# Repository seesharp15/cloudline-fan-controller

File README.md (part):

# Cloudline AI-CLS6 fan controller

A stand-alone speed controller for the **AC Infinity Cloudline AI-CLS6**
(Cloudline S6) EC inline fan. It uses an **Arduino Nano** and an **AITRIP
1.3″ OLED module with a built-in EC11 rotary encoder**, plugs into the fan's
4-pin Molex control lead in place of the stock controller, and runs entirely
from the fan's own 10 V supply.

| Fan off | Fan running (calibrated) |
|---|---|
|  |  |

## What it does

- **Turn the knob** to set the speed from 0 to 100 %: 1 % per click, or 5 %
  per click when you spin it quickly.
- **Press the knob** to switch the fan on or off.
- **The fan is always off at power-up.** A resistor guarantees this in
  hardware before the Arduino even starts, and the firmware starts OFF.
- **The speed setting is kept while the controller has power.** Off and on
  again returns to the same speed. After a power cut it starts OFF at 50 %.
  Nothing is stored permanently.
- **The display shows:**
  - ON/OFF status in the title bar, which turns solid while the fan is on;
  - **SET**: the speed you asked for, as a bar and a percentage;
  - **ACT**: the measured speed from the fan's tachometer, as a bar and a
    percentage of the fan's calibrated top speed;
  - the measured **RPM**.
- **Power:** taken from the fan's +10 V through a resettable fuse,
  reverse-polarity diode, surge clamp and filtering. The controller draws
  about 35–60 mA.
- **Safety nets:** a watchdog stops the fan and restarts the controller if
  the program ever hangs; a "NO TACH / STALLED" warning appears if the fan is
  told to run but no speed pulses arrive.

> ⚠️ **Read before you build.** AC Infinity does not publish the electrical
> details of the control port. The pin functions and signal levels in this
> project come from other builders' reports, and **whether the 4-pin port
> carries a tachometer signal at all is unconfirmed**. The
> [pre-connection verification](#pre-connection-verification) below takes
> about 20 minutes with a multimeter and tells you whether your fan matches.
> Without a tach signal everything works except the ACT bar and RPM.
> [VERIFICATION.md](VERIFICATION.md) lists exactly what has and has not been
> verified.

## Contents

1. [Documents in this repository](#documents-in-this-repository)
2. [Bill of materials](#bill-of-materials)
3. [Tools](#tools)
4. [Software setup](#software-setup)
5. [Pre-connection verification](#pre-connection-verification)
6. [Step-by-step build](#step-by-step-build) (steps 1–6, then
   [7. first power-up](#step-7-first-power-up-on-the-fan-supply) and
   [8. enclosure](#step-8-fit-it-in-the-enclosure))
8. [Normal operation](#normal-operation)
9. [Troubleshooting](#troubleshooting)
10. [Development and tests](#development-and-tests)
11. [Sources](#sources)

---

## Documents in this repository

| Document | Contents |
|---|---|
| [PINOUT.md](PINOUT.md) | Every pin of every part, power rails, point-to-point wiring list |
| [hardware/schematic.svg](hardware/schematic.svg) ([PNG](hardware/schematic.png)) | Full schematic, every part labelled with reference and value |
| [hardware/wiring.svg](hardware/wiring.svg) ([PNG](hardware/wiring.png)) | Physical wiring view with suggested wire colours, for people who don't read schematics |
| [hardware/bom.csv](hardware/bom.csv) | Parts list with part numbers and prices |
| [hardware/pcb/](hardware/pcb/README.md) | **Single-sided PCB** (1 copper layer) as an alternative to perfboard: KiCad project, Gerbers + drill ready to order, assembly drawing, ordering options |
| [hardware/pcb/fusion/](hardware/pcb/fusion/README.md) | **Milling the PCB in Fusion 360** on a Stepcraft M.1000: STEP + DXF (isolation paths, drill layers), Fusion tool library, CAM setup for UCCNC |
| [hardware/pcb/eagle/](hardware/pcb/eagle/README.md) | **Editable design for Fusion Electronics**: schematic + board in EAGLE format |
| [FAQ.md](FAQ.md) | The questions builders ask: USB + fan power, PWM frequency, other fans, warranty, other boards… |
| [BENCH_TEST.md](BENCH_TEST.md) | Manual test of every requirement, first with a dummy load, then with the fan |
| [VERIFICATION.md](VERIFICATION.md) | Requirements traceability, electrical calculations, pin cross-check, what is verified versus assumed, known limitations, review findings |
| [CHANGELOG.md](CHANGELOG.md) | Changes |
| [firmware/](firmware/) | Arduino sketch. Every setting is in [`config.h`](firmware/cloudline_controller/config.h) |
| [test/](test/) | Host unit tests and simulations ([how to run](test/README.md)) |
| [sim/](sim/) | Wokwi simulator files ([what can and cannot be simulated](sim/README.md)) |

---

## Bill of materials

Prices are approximate (USD, 2026) for single quantities. The full list with
manufacturer part numbers is in [hardware/bom.csv](hardware/bom.csv). Any
part with the same value and rating works; the part numbers are examples.

| Ref | Qty | Part | Value / rating | Example part number | ≈ Cost |
|---|---|---|---|---|---|
| U1 | 1 | Arduino Nano | ATmega328P, 5 V, 16 MHz (CH340 clone is fine) | Arduino A000005, or ELEGOO Nano V3.0 | $8 (clone) |
| U3 | 1 | 1.3″ OLED + EC11 module | SH1106, 128×64, I²C 0x3C, 3.3 V | AITRIP 1.3″ OLED with EC11 (Amazon ASIN B0F87DZ51P) | $10 |
| U2 | 1 | 3.3 V LDO regulator | 250 mA, V<sub>in</sub> ≤ 6 V, TO-92 | Microchip MCP1700-3302E/TO | $0.45 |
| Q1 | 1 | N-channel MOSFET | 60 V, 200 mA, logic-level, TO-92 | onsemi 2N7000TA | $0.30 |
| D1 | 1 | Schottky diode | 1 A, 20 V | 1N5817 | $0.20 |
| D2 | 1 | TVS diode, unidirectional | V<sub>RWM</sub> 11.1 V, 600 W | Littelfuse P6KE13A (P6KE15A if your fan measures > 10.8 V) | $0.45 |
| D3, D4 | 2 | Small Schottky diode | 30 V, 200 mA | BAT85 | $0.30 |
| F1 | 1 | Resettable PTC fuse | 0.2 A hold, 0.4 A trip | Bourns MF-R020 | $0.35 |
| U4 | 1 | I²C level shifter module (BSS138) | 5 V ↔ 3.3 V, bidirectional, 2 channels used | SparkFun BOB-12009 | $4 |
| C1 | 1 | Electrolytic capacitor | 220 µF, 25 V | Panasonic EEU-FR1E221 | $0.40 |
| C2 | 1 | Ceramic capacitor | 100 nF, 50 V, 5 mm lead pitch | TDK FG28X7R1H104KNT06 | $0.25 |
| C3, C4 | 2 | Ceramic capacitor | 1 µF, 25 V, 5 mm lead pitch | TDK FG28X7R1E105KRT06 | $0.60 |
| C5 | 1 | Ceramic capacitor | 10 nF, 50 V, 5 mm lead pitch | TDK FG28X7R1H103KNT06 | $0.25 |
| R1, R2 | 2 | Resistor ¼ W 5 % | 2.2 kΩ | Yageo CFR-25JB-52-2K2 | $0.20 |
| R3 | 1 | Resistor ¼ W 5 % | 220 Ω | Yageo CFR-25JB-52-220R | $0.10 |
| R4, R6 | 2 | Resistor ¼ W 5 % | 10 kΩ | Yageo CFR-25JB-52-10K | $0.20 |
| R5 | (1) | Resistor ¼ W 5 %, **only if check M3 says so** | 4.7 kΩ | Yageo CFR-25JB-52-4K7 | $0.10 |
| R7 | 1 | Resistor ¼ W 5 % | 1 kΩ | Yageo CFR-25JB-52-1K0 | $0.10 |
| J1 | 1 | 4-pin PC "Molex" extension cable | male-to-female, 18–20 AWG | StarTech.com LP4POWEXT12 | $4 |
| — | 1 | Perfboard | 5 × 7 cm, 2.54 mm pitch | any | $1 |
| — | 2 | Female header strip (Nano socket) | 1 × 15, 2.54 mm | Sullins PPTC151LFBN-RC | $2 |
| — | 10 | Female-female jumper wires | 20 cm Dupont, for the OLED module | any | $3 |
| — | — | Hook-up wire | 22 AWG stranded (power), 24–26 AWG stranded (signals), several colours | any silicone wire kit | $8 |
| — | — | Heat-shrink tubing | 2–6 mm assortment, 2:1 | any | $6 |
| — | 1 | Enclosure | ABS box, **inside** at least 75 × 60 × 35 mm (perfboard) or 115 × 90 × 35 mm (PCB, so its corners clear the box's screw posts) | a Hammond 1591-series size chosen from its drawing, or 3D-printed | $8 |
| — | 1 | Cable gland | PG7 | any | $0.50 |
| — | 4 | Nylon standoffs and screws | M2.5 or M3 | any | $1 |
| | | | | **Total** | **≈ $60** |

## Tools

| Tool | Notes |
|---|---|
| Temperature-controlled soldering iron | 330–360 °C, small chisel tip |
| Solder | 0.6–0.8 mm rosin-core |
| **Digital multimeter** | Must measure DC volts, resistance, continuity and **diode test**. A frequency (Hz) range is useful for the tach check but not essential. |
| Wire strippers, flush cutters, tweezers | |
| Heat gun or lighter | For heat-shrink |
| **USB cable for the Nano** | Usually **Mini-USB** (some clones use Micro-USB or USB-C). It must be a **data** cable, not charge-only. |
| Computer | Windows, macOS or Linux, with Arduino IDE 2.x |
| 9 V battery with snap lead (or a 9–10 V bench supply with current limit) | For testing the power section before anything touches the fan. Optional but recommended. |
| 220 Ω 1 W resistor, 4.7 kΩ and 10 kΩ ¼ W resistors, 100 Ω ¼ W resistor | For the pre-connection checks (spares from the parts list work) |
| Small drill / step bit, file | For the enclosure window and knob hole |

---

## Software setup

1. **Install the Arduino IDE 2.x** from <https://www.arduino.cc/en/software>
   (2.3.x or newer).
2. **Board support.** Open *Tools → Board → Boards Manager*, search for
   **Arduino AVR Boards**, and install version **1.8.6**. (It is usually
   already installed; just check the version.)
3. **Library.** Open *Tools → Manage Libraries*, search for **U8g2** (by
   oliver), choose version **2.35.30** in the version drop-down, and click
   *Install*. No other library is needed. The pinned versions are listed in
   [firmware/libraries.txt](firmware/libraries.txt).
4. **Open the sketch.** *File → Open* →
   `firmware/cloudline_controller/cloudline_controller.ino`. Five tabs open:
   `cloudline_controller.ino`, `app.cpp`, `config.h`, `display_ui.h`,
   `fan_logic.h`. The folder must stay named `cloudline_controller`.
5. **Select the board.** *Tools → Board → Arduino AVR Boards → Arduino
   Nano*.
6. **USB driver (clone Nanos).** Most clones use a **CH340** USB chip. Plug
   the Nano in and look at *Tools → Port*:
   - A new port appears (`COM3`… on Windows, `/dev/cu.usbserial-…` or
     `/dev/cu.wchusbserial…` on macOS, `/dev/ttyUSB0` on Linux): fine, select it.
   - No new port: install the CH340 driver (**CH341SER**) from the chip maker,
     WCH: <https://www.wch-ic.com/downloads/CH341SER_EXE.html> (Windows) or
     <https://www.wch-ic.com/downloads/CH341SER_MAC_ZIP.html> (macOS), then
     replug. Linux needs no driver. If still nothing, try another USB cable:
     many are charge-only.
7. **Processor setting.** *Tools → Processor* has two choices:
   - **"ATmega328P"**: genuine Nanos and newer clones (Optiboot bootloader,
     uploads at 115200 baud).
   - **"ATmega328P (Old Bootloader)"**: most older and cheap clones
     (uploads at 57600 baud).

   **How to tell:** start with *ATmega328P* and click *Upload* (with any
   sketch, e.g. *File → Examples → 01.Basics → Blink*). If it ends with an
   error like `avrdude: stk500_recv(): programmer is not responding` or
   `not in sync: resp=0x00` after about 10 tries, switch to *Old Bootloader*
   and upload again. Whichever one works is the one you have. The watchdog in
   this firmware is designed to work with both (see
   [FAQ](FAQ.md#what-does-the-watchdog-do-and-is-it-safe-with-the-old-bootloader)).
8. **Compile once** (*Sketch → Verify*). Expected result, give or take a
   few bytes depending on IDE and library versions:

   ```
   Sketch uses 26236 bytes (85%) of program storage space. Maximum is 30720 bytes.
   Global variables use 1287 bytes (62%) of dynamic memory, leaving 761 bytes for local variables. Maximum is 2048 bytes.
   ```

   ("Old Bootloader" shows the same numbers.) Don't upload yet: that is
   build step 5.

Command-line alternative:

```sh
arduino-cli core install arduino:avr@1.8.6
arduino-cli lib install "U8g2@2.35.30"
arduino-cli compile -b arduino:avr:nano firmware/cloudline_controller
arduino-cli upload  -b arduino:avr:nano -p <port> firmware/cloudline_controller
# old bootloader: -b arduino:avr:nano:cpu=atmega328old
```

---

## Pre-connection verification

Do this **before you build anything**, on the fan itself. It confirms the
pin functions, the supply, and the speed signal. You need the multimeter, the
fan plugged into mains, and the resistors listed under Tools. Nothing here
can damage the fan: every test either just measures or goes through a
resistor.

**Setup.** Unplug the stock controller from the fan's control lead. Look
into the lead's 4-pin Molex plug with the two chamfered corners at the top
and number the contacts **1 to 4 from left to right** (picture in
[PINOUT.md §2](PINOUT.md#2-j1-fan-connector-4-pin-molex-pc-peripheral-type-508-mm-pitch)).
The fan may run at full speed while nothing is plugged in. That is expected
and is one of the things being checked. Probe the contacts from the front
with thin probe tips, or plug in the J1 extension cable and probe its loose
end (then follow the wires back to be sure which is which).

Record every reading in a table like the one below; you'll need them later.

| Check | How | Expected | If not → STOP and… |
|---|---|---|---|
| **M1 Supply and ground** | DC volts, black probe on pin 3, red on pin 4 | **+9.5 to +10.5 V** | **Negative reading:** you are numbering from the wrong side; mirror the numbers and repeat. **No pin pair gives 9–11 V:** your fan's port is different (for example a newer USB-C "UIS" port, see [FAQ](FAQ.md#will-this-work-with-other-ac-infinity-fans-or-other-4-pin-fans)). Don't connect. **10.8–12 V:** fit a P6KE15A for D2 instead of P6KE13A. **Over 12 V:** don't connect; the design needs changes. |
| **M2 Supply under load** | Hold a **220 Ω 1 W** resistor across pins 4 and 3 for 5 s and measure pins 4–3 again | Within **0.5 V** of M1 (45 mA load, more than the controller draws) | Drop of more than 1 V: the port can't power the controller. Power the Nano from a separate 9–12 V adapter (FAQ) and leave J1 pin 4 unconnected. |
| **M3 Speed line pull-up** | DC volts, pin 3 (black) to pin 2 (red), nothing else connected | **About the same as M1** (an internal pull-up to the fan's supply) | **Below 1 V or drifting:** the line floats. Fit R5 (4.7 kΩ). **Above M1 + 0.5 V:** don't connect. |
| **M3b Pull-up strength** | Connect a **10 kΩ** resistor from pin 2 to pin 3 and measure pins 2–3 | **Between 1 V and 0.9 × M1** (the internal pull-up is between about 1.1 kΩ and 100 kΩ). Note the value: pull-up R ≈ 10 kΩ × (M3 ÷ reading − 1). While connected, watch the fan for M4b. | **Below 0.1 V:** the pull-up is very weak (> 1 MΩ); fit R5. **Above 0.9 × M1:** pin 2 is a stiff source, not a pulled-up control line. Don't do M4; recheck the numbering. |
| **M4b PWM or analogue input?** | Take the pull-up value you worked out in M3b and connect a resistor of about that value (nearest standard value) from pin 2 to pin 3. The line now sits near **half of M1** (measure it). Wait 15 s and listen. | Either result is fine; note which. **Fan settles at a clearly in-between speed:** the input reacts to the average voltage (analogue-style); the 4 kHz PWM's average does the same job. **Fan runs at full speed or stops:** it is a switching (logic) input, which is what PWM expects. | If later (bench B4) the speed hunts or surges at mid settings, the input is analogue without filtering. Add an RC filter: a series resistor between Q1's drain and J1 pin 2 of **at most 1/20 of the M3b pull-up** (e.g. 470 Ω for a 10 kΩ pull-up), and a capacitor from J1 pin 2 to GND so that the series R × C ≥ 2.5 ms (e.g. 10 µF with 470 Ω). A larger series resistor would stop 0 % / OFF from pulling the line low enough to stop the fan. Re-run M4 and bench B4, B7. |
| **M4 Polarity and stop** | Connect pin 2 to pin 3 through a **100 Ω** resistor. Wait 15 s. Remove it. Wait 15 s. | Linked: the fan **slows down and stops** (it may coast for several seconds). Released: it **speeds up to full**. | **Opposite** (linked = full, released = stop): set `FAN_PWM_INVERTED 0` in `config.h` **and** connect R4 (at the D9 end of R3) to GND instead of +5V. **Linked = slow but never stops:** this fan does not stop at 0 %; OFF will mean "minimum speed" ([FAQ](FAQ.md#does-0-or-off-actually-stop-the-fan)). **No change at all:** pin 2 isn't the speed line; recheck the numbering. |
| **M5 Tach pin** | Fan at full speed (pin 2 released). DC volts pin 3 (black) to pin 1 (red). If your meter has Hz, measure that too. Then connect a **10 kΩ** resistor from pin 1 to pin 4 and repeat. Then stop the fan (100 Ω link on pin 2) and repeat. | A tach shows up as a **frequency of roughly 10–200 Hz while running** (or a steady DC reading between 2 and 8 V that changes when the fan stops), at least with the 10 kΩ pull-up connected. Write down the frequency at full speed. | **Steady 0 V, no frequency in any case:** no tach on this port. The controller still works; ACT shows `--%`. **Steady voltage equal to M1 that doesn't change:** not a tach (another supply pin); it is still safe to connect (R7 limits the current) but there will be no RPM. **Above 12 V:** don't connect pin 1; leave R7 unconnected at J1. |
| **M5b Tach type and pulses per revolution** (optional) | From M5: a frequency **without** the 10 kΩ pull-up means a **push-pull** output (note its high voltage: DC reading ≈ half of it); a frequency only **with** the pull-up means **open collector**. For pulses per revolution you need the true RPM: an optical (laser) tachometer on a piece of reflective tape on the impeller, or a phone slow-motion video of a marked blade at a low setting (count turns per second). PPR = frequency × 60 ÷ RPM. | Usually 1, 2 or 4. Put it in `TACH_PULSES_PER_REV`. | If you can't measure it, leave 2: only the RPM number is affected, not the ACT %. |
| **M6 No short to mains** | Unplug the fan from mains. Ohms, each pin 1–4 to each mains plug blade | **Open circuit (OL)** on every combination | Any reading: the fan is faulty or the port is not isolated. Do not use it. |

**M7 OLED module** (no power needed). With the module unpowered: resistance
VCC to GND **above 1 kΩ**; SDA to VCC and SCL to VCC: either **OL** (no
pull-ups on the module) or **2–10 kΩ** (pull-ups fitted), both fine; TRA,
TRB to GND: **toggles between OL and about 0 Ω** as you turn the knob slowly
(at rest either can be open or closed, depending on the encoder type); PSH to
GND: **OL**, and **0 Ω while pressed**. They are plain switches to GND. If a
pin reads a fixed resistance to VCC instead, the module has its own pull-ups
on the encoder, which is also fine. If SDA/SCL read **4.7 kΩ or less** to
VCC (strong pull-ups already on the module), leave **R1/R2 out** in step 4:
with them as well, the display-side pull-ups would sink more than the 3 mA
I²C allows. The display driver (SH1106 vs SSD1306) and the I²C
address can't be measured with a meter: build step 5 checks them (the
serial console reports which address answers).

When all checks pass, plug the stock controller back in if you still want to
use the fan, and start the build.

---

## Step-by-step build

These steps describe a perfboard build. With the [PCB](hardware/pcb/README.md)
the order and the checks are the same; its README lists which parts go in
at each step.

Build in this order. Each step ends with a check: **don't continue until the
check passes.** The schematic shows every connection; the
[wiring view](hardware/wiring.png) shows where wires go physically; the
[point-to-point list](PINOUT.md#6-point-to-point-wiring-list) is a checklist.

Soldering basics: heat the pad and the lead together for 2–3 s, feed solder
into the joint (not onto the iron), and stop when it flows into a small
shiny cone. Trim leads after soldering. Diodes: the **band is the cathode**.
The electrolytic capacitor: the **stripe marks the negative** lead. TO-92
parts (Q1, U2): read the flat face, legs down, left to right (PINOUT.md §5).

### Step 1. Verify the fan connector

Do the [pre-connection verification](#pre-connection-verification) M1–M6 and
write down the results. Then prepare **J1**: cut the Molex extension cable in
half, keep the end that plugs into the fan's lead, strip 5 mm from each wire,
and **label each wire with its pin number and function** (tape flags). Put
heat-shrink on the cable end.

✅ **Check before continuing:** with J1 plugged into the fan (fan powered),
J1's labelled "+10V" wire reads the M1 voltage against its "GND" wire. Then
unplug J1 from the fan.

### Step 2. Build the power conditioning

On the perfboard, plan three areas (power on the left, Nano socket in the
middle, fan interface near the J1 entry). Solder:

1. the two 15-pin female headers for the Nano socket, 15.24 mm (6 holes) apart;
2. **F1** (PTC), **D1** (1N5817, band towards the Nano VIN side),
   **D2** (P6KE13A, band to +10V_P, other end to GND),
   **C1** (220 µF, stripe to GND), **C2** (100 nF, close to the socket's VIN
   and GND pins);
3. wires: J1 "+10V" to F1, J1 "GND" to the board's GND line, +10V_P to the
   socket's **VIN** pin (30), GND to the socket's **GND** pins (29 and 4).

Do **not** connect J1's PWM and TACH wires yet. Insulate their ends with
heat-shrink.

Before soldering D1 and D2, check them on the meter's diode range: D1
(1N5817) reads **0.15–0.35 V** with red on the plain end and black on the
band, **OL** the other way round; D2 (P6KE13A) reads **0.5–0.8 V** with red
on the plain end, **OL** reversed.

✅ **Check before continuing** (nothing powered):
- Resistance with **red on +10V_P** and black on GND: **not below 1 kΩ** (it
  climbs as C1 charges from the meter, which is normal). With the probes
  reversed you'd see D2 conducting, which is also normal.
- Continuity J1 "GND" to socket pin 29 and pin 4: **beep (< 1 Ω)**.
- Continuity J1 "+10V" to socket pin 30: **no beep** (D1 is in the way).

### Step 3. Test the power section with no Nano

Leave the Nano out of its socket. Connect a 9 V battery (or a bench supply
set to 10.0 V, current limit 100 mA) to J1's +10V and GND wires.

✅ **Check before continuing:**
- Socket VIN (pin 30) to GND: **battery voltage minus 0.05–0.3 V** (D1's
  drop at almost no current; about 9.2 V on a fresh 9 V battery, about
  9.8 V on a 10 V supply).
- Supply current, if your supply shows it: **under 1 mA**.
- **Reverse-polarity test:** swap the battery leads. Socket VIN now reads
  **0 V (±0.1 V)**. D1 is blocking. Swap back.
- D2 and C1 are **not warm** after a minute.

If you'd rather use the fan as the source: plug J1 into the fan with only
the +10V and GND wires attached (PWM and TACH still insulated). Expect VIN =
**M1 minus 0.05–0.3 V**. The fan runs at full speed during this test because
nothing holds its speed line low. Unplug J1 afterwards.

### Step 4. Wire the 3.3 V regulator, OLED and encoder

1. Solder **U2** (MCP1700, flat face towards you: GND, VIN, VOUT),
   **C3** (VIN to GND) and **C4** (VOUT to GND). Wire U2 VIN to the socket's
   **+5V** pin (27).
2. Solder header pins to **U4** (the level-shifter module) and mount it on
   the perfboard. Wire **HV** to +5V (socket pin 27), **LV** to U2 VOUT
   (+3V3), **GND** to GND, **HV1** to socket **A4** (pin 23), **HV2** to
   socket **A5** (pin 24). U4 lets the 5 V Nano and the 3.3 V display talk
   without either seeing the other's voltage.
3. Solder **R1** (U2 VOUT to U4 **LV1**) and **R2** (U2 VOUT to U4 **LV2**),
   unless check M7 found 4.7 kΩ or less pull-ups on the module.
4. Run the module wires, **matching the labels printed on your module**
   (the pin order varies between batches):

   | Module | To | Suggested colour |
   |---|---|---|
   | VCC | U2 VOUT (+3V3) | pink |
   | GND | GND | black |
   | SDA | U4 LV1 (and R1); U4 HV1 goes to socket A4 (pin 23) | blue |
   | SCL | U4 LV2 (and R2); U4 HV2 goes to socket A5 (pin 24) | white |
   | TRA | socket D3 (pin 6) | purple |
   | TRB | socket D4 (pin 7) | grey |
   | PSH | socket D5 (pin 8) | cyan |
   | CON | socket D6 (pin 9) (optional) | light blue |
   | BAK | socket D7 (pin 10) (optional) | violet |

✅ **Check before continuing** (nothing powered, Nano out):
- Continuity from each module pin to its socket pin in the table: **beep**
  (for SDA/SCL: module to U4 LV1/LV2, and U4 HV1/HV2 to A4/A5).
- No continuity between neighbouring socket pins D3–D7, or A4–A5.
- No continuity from socket A4 to module SDA (U4 is in between: you'll read
  several kΩ, not a beep).
- Resistance socket +5V (27) to GND: **above 1 kΩ**.
- Resistance module VCC to GND: **above 1 kΩ**.
- Resistance module SDA to module VCC: **2.2 kΩ or less** (R1, perhaps in
  parallel with a pull-up on the module).

### Step 5. Flash and test with USB power only

J1 must **not** be connected to anything.

**Orientation check before plugging in the Nano.** In step 2 you wired one
socket hole to +10V_P (via D1) and the hole next to it to GND; in step 4 you
wired a hole three places further along to +5V. Hold the Nano over the
socket: the pins printed **VIN**, **GND** and **5V** must sit over exactly
those holes. Turned round the other way, VIN would land on D12 and the
Nano could be damaged as soon as the fan powers it. Then plug the Nano in,
connect USB, select the port and processor (Software setup step 7), and
click **Upload**.

✅ **Check before continuing:**
- The IDE ends with `Done uploading` (or avrdude reports
  `... bytes of flash verified`).
- Within 1 s the display shows **`FAN OFF`** in an outlined title bar,
  **`0 RPM`** at the right, **SET** bar at **50%**, **ACT** at **`--%`**, and
  the footer **`Press knob to start`** (like the left picture at the top).
- Multimeter: socket +5V to GND **4.5–5.1 V** (USB minus the Nano's diode);
  module VCC to GND **3.25–3.35 V**.
- Turn the knob slowly one click clockwise: SET becomes **51%**. One click
  back: **50%**. If it goes the wrong way, set `ENC_REVERSE 1` in `config.h`
  and upload again. If every *other* click is ignored, set
  `ENC_EDGES_PER_DETENT 2`.
- Press the knob once: title becomes a solid **`FAN ON`** and the Nano's
  **L** LED (D13) lights. After 8 s the footer shows
  **`! NO TACH / STALLED`**: correct, there is no fan yet. Press again: back
  to `FAN OFF`, LED off.
- *Tools → Serial Monitor*, **115200** baud, line ending **Newline**. On
  reset it prints `Cloudline controller ready. Fan OFF. Send ? for help.`
  and **`OLED answers at 0x3C`**. Type `s` and Enter: a status line
  starting `on=0 set=50%` appears.
- Display driver: the picture is sharp and centred with no column of random
  dots at either edge. If there is one, your module has an SSD1306: set
  `OLED_SSD1306 1` and upload again.

### Step 6. Wire the fan interface

Unplug USB. Solder:

1. **Speed output:** **Q1** (2N7000, flat face towards you: S, G, D);
   **R3** 220 Ω from socket **D9** (pin 12) to Q1 gate; **R4** 10 kΩ from
   the **D9 end of R3** to **+5V**; Q1 source to GND; J1 **PWM** wire to Q1 drain.
   Fit **R5** (Q1 drain to J1's +10V wire, before F1) only if check M3
   told you to.
2. **Tach input:** **R7** 1 kΩ from J1 **TACH** wire to the tach node;
   from the tach node: **R6** 10 kΩ to +5V, **D3** BAT85 (band to +5V),
   **D4** BAT85 (band to the tach node, other end GND), **C5** 10 nF to GND,
   and a wire to socket **D2** (pin 5). If M5 found more than 12 V on pin 1,
   leave the TACH wire unconnected.

✅ **Check before continuing** (J1 still unplugged from the fan; USB
connected, so the Nano runs):
- Q1 gate (the R3/Q1 junction) to GND with the display at **`FAN OFF`**:
  **4.5–5.1 V**. Gate high means Q1 is on, which means the fan line is held
  low.
- Press the knob (`FAN ON`), turn SET to **100%**: gate **below 0.1 V**.
- SET **50%**: the meter (DC volts) shows about **half the 5 V reading**
  (2.2–2.6 V). It is averaging the 4 kHz PWM.
- Switch OFF again. Resistance with the **red** probe on J1 **PWM** and the
  **black** probe on J1 **GND**: **below 20 Ω** (Q1 is on). Switch ON at
  100 %: **above 1 MΩ** or OL (Q1 is off). With the probes the other way
  round you'd measure Q1's internal diode instead. (Skip this if R5 is
  fitted; Step 7 and BENCH_TEST cover it with voltages.)
- Tach node (socket D2) to GND: **4.5–5.1 V** (R6 pull-up).
- Touch J1 **TACH** to J1 **GND** for a moment: the tach node drops to
  **about 0.45 V** while touching. Press **CON** (or hold the knob while
  pressing reset) to open the diagnostics page: the **`n=`** counter at top
  right goes up each time you touch.

---

## Step 7. First power-up on the fan supply

1. Unplug USB from the Nano. Unplug the fan from mains.
2. Plug J1 into the fan's control lead.
3. Plug the fan into mains.

**What you should see within about 1 second:**

| | Expected |
|---|---|
| Fan | **Not running.** If it was spinning, it coasts to a stop. |
| Display | **`FAN OFF`**, `0 RPM`, SET **50%**, ACT **`--%`**, footer **`Press knob to start`** |
| Nano LED L (D13) | off |
| +10V_P (socket VIN) to GND | **M1 minus 0.2–0.7 V** |
| +5V (socket 27) to GND | **4.9–5.1 V** |
| Module VCC to GND | **3.25–3.35 V** |

Then:

4. **Press the knob.** `FAN ON` (solid title bar). The fan starts at 50 %.
   Within 1–3 s the RPM figure shows a number; ACT stays at `--%` because the
   fan's top speed isn't known yet, and the footer reads
   **`Hold knob 3s: CAL`**. (No RPM after 8 s and the footer says
   `! NO TACH / STALLED`? See [Troubleshooting](#troubleshooting).)
5. **Turn the knob** to 100 % and back to 20 %: the fan speeds up and slows
   down within a few seconds (EC fans ramp gently).
6. **Calibrate** (needs a tach): set any speed, then **hold the knob for 3
   seconds** until the footer countdown finishes. The fan runs at 100 % for
   18 s (12 s spin-up, 6 s measuring) and shows **`CAL DONE`** with the
   top-speed RPM. Then ACT shows real percentages.
7. **Press the knob.** `FAN OFF`, the fan stops.
8. Unplug the fan from mains, wait 10 s, plug it back in. The controller
   comes up **OFF at 50 %** again.

✅ **Check before continuing:** every row of the table above matched, and
steps 4–8 behaved as described.

Optional, recommended: work through [BENCH_TEST.md](BENCH_TEST.md), which
tests every requirement one by one.

## Step 8. Fit it in the enclosure

Unplug the fan from mains first. Cut a window for the OLED and a hole for
the encoder shaft (usually 7 mm), fit the cable gland for J1, mount the
perfboard and the module on standoffs, and make sure the Nano's USB socket
can still be reached. Tie a knot or use the gland so a pull on the fan cable
can't reach the solder joints. Check that no bare lead touches another or
the Nano's underside.

✅ **Check before continuing:** plug the fan back into mains. The display
shows `FAN OFF` and the fan doesn't run; press the knob and it runs.

---

## Normal operation

| Control | What it does |
|---|---|
| Turn the knob | Change the speed setting. 1 % per click; 5 % per click if you turn quickly. Works while OFF too (the fan stays off). |
| Press the knob (short) | Fan ON / OFF. The toggle happens when you **release** the knob, so that a long hold can start a calibration instead. |
| Hold the knob 3 s (fan ON) | Calibrate the top speed. Press the knob or BAK to cancel. |
| CON key | Diagnostics page (raw tach Hz, pulse count, line duty, PWM register values). CON or BAK returns. |
| BAK key | Back to the main screen; cancels a calibration. |
| Knob held while powering up | Start on the diagnostics page (that press doesn't switch the fan on). |

**The screen** (refreshes 10 times a second, and immediately after you
turn or press the knob):

| Screen | Meaning |
|---|---|
|  | Fan OFF. SET shows the speed it will run at when switched on. |
|  | Fan ON, RPM measured, top speed not calibrated yet: ACT shows `--%`. |
|  | Fan ON and calibrated. The thin vertical line in the ACT bar marks the SET value. |
|  | The fan was told to run but no tach pulses arrived for 8 s. |
|   | Calibration countdown, and the calibration run. |
|   | Calibration result. |
|  | Diagnostics page. |

**Keeping the calibration.** By design nothing is stored permanently, so a
calibration lasts until power-off. To make it permanent, connect USB once,
open the Serial Monitor (115200 baud) and calibrate: it prints a line such as
`#define TACH_MAX_RPM 1836`. Put that number into `config.h` and upload again.

**Serial console** (115200 baud, Newline): `?` help · `s` status ·
`on` / `off` · `set 40` · `c` calibrate (fan must be on) · `x` cancel ·
`m 1836` set top speed for this session. You can leave USB connected while
the fan is plugged in ([FAQ](FAQ.md#can-i-power-the-nano-from-usb-and-the-fan-at-the-same-time)).

---

## Troubleshooting

| Symptom | Likely cause | Fix |
|---|---|---|
| **Blank display**, LED L works (the controller keeps working without a display and looks for it again every 5 s) | No 3.3 V at the module; SDA/SCL swapped or not connected; U4 not powered; module at address 0x3D; wrong module pin order | Open the Serial Monitor: it says whether a display answers and at which address (`OLED answers at 0x3C`, or `! but a device answers at 0x3D`). Measure module VCC (3.25–3.35 V) and U4 HV (5 V) / LV (3.3 V). Check SDA/SCL by label, not position. |
| **Blank display**, nothing works | No power: F1 tripped, D1 reversed, J1 wires swapped | Measure VIN (Step 3 values). Unplug, let F1 cool for a minute, look for a short. |
| **Garbled display** (random dots, shifted picture, a column of noise at one edge) | Your board has an SSD1306, not an SH1106 | Set `OLED_SSD1306 1` in `config.h` and upload. |
| **Garbled display** that changes when the fan starts | Noise or a poor ground on the I²C wires | Keep the OLED wires short (< 30 cm) and away from the fan cable; check the GND wire to the module. |
| **Encoder skips** clicks (every other click ignored) | Encoder has 2 edges per click (15 pulses / 30 detents type) | `ENC_EDGES_PER_DETENT 2` |
| **Encoder jumps 2 per click** | The opposite: `ENC_EDGES_PER_DETENT` is 2 on a 20/20 encoder | `ENC_EDGES_PER_DETENT 4` |
| **Encoder runs backwards** | A/B swapped (module orientation) | `ENC_REVERSE 1`, or swap the TRA/TRB wires |
| **Encoder erratic** | Loose TRA/TRB/GND wire | Recheck Step 4 continuity |
| **Button doesn't toggle** | PSH not on D5, or no GND to the module | Continuity PSH → D5. Note the toggle happens on **release**; if you hold for 3 s it starts a calibration instead (only while ON). |
| **Button toggles twice** | Should not happen: presses are debounced (25 ms). If it does, the switch is failing. | Raise `BUTTON_DEBOUNCE_MS` to 50. |
| **Fan runs at full speed when it should be off** (display says FAN OFF) | Q1 not pulling the line low: Q1 backwards, R4 missing, PWM wire on the wrong J1 pin, or polarity opposite | Q1 gate should read ~5 V while OFF (Step 6). Check 2N7000 pin order S-G-D. Recheck M4; if the fan runs when the line is low, use `FAN_PWM_INVERTED 0` and R4 to GND. |
| **Fan runs at full speed for a moment at power-up** | R4 missing or wired to the wrong place | R4 must go from the D9 end of R3 to +5V. |
| **Fan won't stop at 0 % / OFF** (runs slowly) | This fan's minimum speed is above zero when the line is low (M4) | Expected for that fan: see [FAQ](FAQ.md#does-0-or-off-actually-stop-the-fan). |
| **Fan won't stop and runs at full** | See "full speed when it should be off" | |
| **Fan doesn't start at low settings** | EC fans need a minimum duty to start | Raise `FAN_DUTY_MIN_PCT` to the lowest duty that turns it (BENCH_TEST B6). |
| **Speed tops out at about half** | Line not reaching the fan's high level: R5 fitted when not needed, or something else loads the line | Remove R5 if M3 read ~10 V. Q1 must be fully off at 100 % (gate < 0.1 V). |
| **RPM reads 0 / "NO TACH"** while the fan clearly turns | No tach on this port (M5), TACH wire on the wrong pin, D4 backwards, or `TACH_FAULT_MS` too short for a slow-starting fan | Diagnostics page: does `n=` count? Recheck M5. D4 band must face the tach node. |
| **RPM erratic** or jumps | Noise on the tach wire, or a tach signal with slow edges | Route the tach wire away from mains; C5 must be fitted. Increase `TACH_WINDOW_MS` to 1000 or `TACH_SMOOTHING` to 8. |
| **RPM is exactly double or half the real speed** | Pulses per revolution differ from 2 | Change `TACH_PULSES_PER_REV` (ACT % is unaffected; it uses the calibration). |
| **ACT always `--%`** while RPM shows | Not calibrated in this power session | Hold the knob 3 s while ON, or set `TACH_MAX_RPM` in `config.h` |
| **CAL FAILED** | No tach, or the speed varied by more than ±10 % at 100 % (gusty ducting, fan still ramping) | Check the tach; close doors/vents; try again. Raise `CAL_SPINUP_MS` for a slow fan. |
| **Nano resets when the fan changes speed** (display flickers back to FAN OFF) | The fan's 10 V dips under load changes; poor connection in J1; C1 missing | Check J1 crimp and solder joints. C1 must be 220 µF or more (470 µF is fine). Measure VIN during a speed change: it must stay above 6.5 V. |
| **Display goes back to FAN OFF on its own**, serial says `restarted by the watchdog` | The program stalled for 2 s (should not happen) | Note what you were doing and open an issue. The fan is safely OFF after a restart. |
| **Upload fails** (`not in sync`, `programmer is not responding`) | Wrong processor setting, wrong port, charge-only cable, Serial Monitor holding the port | Try the other *Processor* option (Software setup step 7). Check *Tools → Port*. Close the Serial Monitor. Try another cable. |
| **Upload fails**, port missing | CH340 driver missing | Install CH341SER (Software setup step 6). |
| **Upload fails** only when the fan is connected | Shouldn't happen; check for a short pulling down D0/D1 | Unplug J1 and retry. |
| **Compile error** `U8g2lib.h: No such file` | Library not installed | Software setup step 3. |
| **Compile error** about `FAN_PWM_FREQ_HZ`, pins, or duty limits | A `config.h` value is out of range | The error message names the setting. |

---

## Development and tests

```sh
make -C test                    # host unit tests + firmware simulation (any C++17 compiler)
sh test/avr/run_simavr.sh       # real Nano binary in simavr (needs arduino-cli and simavr)
make -C test shots              # regenerate docs/img/screen_*.svg from the real drawing code
python3 hardware/schematic.py   # regenerate the schematic (SVG + PNG)
python3 hardware/wiring.py      # regenerate the wiring view
python3 hardware/overview.py    # regenerate the overview illustration
```

The recorded test output, compile size report and review results are in
[VERIFICATION.md](VERIFICATION.md).

Repository layout:

```
├── README.md  FAQ.md  PINOUT.md  BENCH_TEST.md  VERIFICATION.md  CHANGELOG.md  TASK.md
├── firmware/
│   ├── libraries.txt                 pinned core and library versions
│   └── cloudline_controller/
│       ├── cloudline_controller.ino  (no code: see the comment inside)
│       ├── config.h                  every tunable value and pin
│       ├── app.cpp                   hardware glue: setup/loop, ISRs, PWM, watchdog, serial
│       ├── fan_logic.h               pure logic (unit-tested on the host)
│       └── display_ui.h              screen layouts
├── test/        host tests, stubs, AVR simulation script
├── hardware/    schematic/wiring/overview sources (.py) and renders (.svg/.png), bom.csv
├── sim/         Wokwi diagram.json, wokwi.toml, libraries.txt
└── docs/img/    display screenshots (generated by the tests)
```

## Sources

- [RollItUp: ESP32 control of Cloudline EC fans](https://www.rollitup.org/t/idiots-guide-to-getting-an-esp32-to-control-ac-infinity-cloudline-ec-fans-esphome-ha.1053910/): PC-style 4-pin Molex, MOSFET low-side drive, `inverted: true`, 1 kHz works
- [RollItUp: Cloudline T6 / Hyperfan pin numbering](https://www.rollitup.org/t/how-i-hooked-up-pwm-singals-to-acinfinity-cloudline-t6-and-hyperfan-8-from-an-open-source-software.1037278/): pin 4 = +10 V, 3 = GND, 2 = PWM, 1 = not used, chamfer up, left to right
- [RollItUp: Cloudline AI-CLS6 PWM control with RPi](https://www.rollitup.org/t/cloudline-ai-cls6-s6-pwm-control-with-rpi.1046753/): 10 V provided by the fan; 100 % PWM through a transistor = off
- [chriskoz/AutoFan](https://github.com/chriskoz/AutoFan) (Cloudline S6): "4-pin molex ATX HDD connector", control wire "pulled up to 10V by the fan", stock controller ≈ 245 µs period (~4 kHz)
- [coofercat/ha-ac-infinity-fan](https://github.com/coofercat/ha-ac-infinity-fan): newer USB-C "UIS" S6: +10 V, tach on D+, PWM on D−, ~5 kHz
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
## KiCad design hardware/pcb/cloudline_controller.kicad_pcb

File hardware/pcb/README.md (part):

# Cloudline controller PCB: from files to finished board

The controller on a printed circuit board instead of perfboard:

- **one copper layer** (the bottom), no wire links;
- all parts through-hole, on the top;
- 100 × 75 mm, four M3 mounting holes.

It carries every part in [the schematic](../schematic.svg), plus a 4-way screw
terminal for the fan cable and two pin headers for the OLED module.

This page covers everything about the board:

- the three ways to get a board made, and every file involved;
- a **walkthrough in separate sessions**, from opening the files to a
  finished, boxed controller;
- reference: design notes, how the board was checked, regenerating the files.

| Top (parts side) | Bottom copper (as seen from below) |
|---|---|
|  |  |

> **Status: designed and checked, not yet made.** The files pass KiCad's
> design-rule check, an independent copper-connectivity check, an independent
> review, and the milling and EAGLE export checks below. No board has been
> built from them yet, and nothing has been opened in Fusion 360 or run on the
> machine. Build the first one expecting to find something.

## Contents

1. [Three ways to get a board](#three-ways-to-get-a-board)
2. [Your setup (milling)](#your-setup-milling)
3. [Files](#files)
4. [The walkthrough, session by session](#the-walkthrough-session-by-session)
   - [How the sessions work](#how-the-sessions-work) · [Progress log](#progress-log)
   - [S0 Gather materials](#s0-gather-materials-and-check-the-fan)
   - [S1 Get the files](#s1-get-the-files)
   - [S2 Review or edit in Fusion Electronics (optional)](#s2-review-or-edit-in-fusion-electronics-optional)
   - [S3 Prepare and measure the blank](#s3-prepare-and-measure-the-blank)
   - [S4 Fusion: import](#s4-fusion-import-model-tools-isolation-paths)
   - [S5 Fusion: setup and operations](#s5-fusion-setup-and-operations)
   - [S6 Fusion: simulate and post](#s6-fusion-simulate-and-post)
   - [S7 Machine: prepare, mount, zero](#s7-machine-prepare-mount-zero)
   - [S8 Machine: isolation](#s8-machine-isolation-t1)
   - [S9 Machine: drilling](#s9-machine-drilling-t2t6)
   - [S10 Machine: outline](#s10-machine-outline-t7)
   - [S11 Clean, inspect, test the bare board](#s11-clean-inspect-and-test-the-bare-board)
   - [S12–S17 Assembly and first power-up](#s12s17-assembly-and-first-power-up)
   - [S18 Enclosure](#s18-enclosure)
5. [Ordering from a board house](#ordering-from-a-board-house)
6. [Design notes](#design-notes) · [Verification](#verification) · [Regenerating](#regenerating)

## Three ways to get a board

| Route | Use | Sessions |
|---|---|---|
| **A. Mill it** on the Stepcraft M.1000 with Fusion 360 | Files in [`fusion/`](fusion/README.md) | S0 → S18, all of them |
| **B. Order it** from a board house | Upload [`fab/cloudline_controller_RevB_gerbers_drill.zip`](fab/cloudline_controller_RevB_gerbers_drill.zip), see [Ordering](#ordering-from-a-board-house) | S0, S1, order, then S11 → S18 |
| **C. Etch it** at home by toner transfer | Print [`fab/bottom_copper_toner_transfer_1to1.pdf`](fab/bottom_copper_toner_transfer_1to1.pdf) at 100 % | S0, S1, etch, drill by hand, then S11 → S18 |

To **change the circuit or the layout**, use Fusion Electronics (session S2).
The milling files in `fusion/` and the Gerbers in `fab/` are made from the
KiCad copy of the board. They don't change when you edit in Fusion. See
[Which copy is master](#which-copy-is-master).

## Your setup (milling)

The milling files and the walkthrough are made for this setup:

| | |
|---|---|
| Machine | Stepcraft M.1000 with tool changer |
| Control software | UCCNC (Autodesk's *UCCNC* post in Fusion) |
| Spindle | Stepcraft DI 1000, 8 000–20 000 rpm |
| CAM | Fusion 360, commercial licence: one program with all tool changes, real rapids |
| Blank | FR-4; thickness is measured in S3; the copper weight doesn't matter (the cut works for 35 and 70 µm) |
| Workholding | Double-sided tape, Z touch plate, **no height map** |
| Tools (T1–T7) | T1 V-bit 30° with 0.1 mm tip · T2 0.8 mm drill · T3 1.0 · T4 1.2 · T5 1.3 · T6 3.2 · T7 2 mm 2-flute end mill |

**Assumed and to confirm:**

- the V-bit's angle and tip;
- the outline end mill size;
- the tool numbers in your changer.

[S4](#s4-fusion-import-model-tools-isolation-paths) says how to change any of these.

**Board numbers that matter for milling:**

- **Gaps:** the smallest gap between copper of different nets is **0.64 mm**.
  It sits between neighbouring 2.54 mm-pitch header pads, and no layout can
  make it larger. Tracks keep at least 0.69 mm from other copper. Copper is
  at least 3.15 mm from the board edge.
- **Isolation cut:** two passes with the V-bit, **0.20 mm deep**,
  0.207 mm wide. That clears about 0.33 mm around every pad and track.
  - The paths were simulated for a board up to **±0.10 mm** off the Z
    touch-off height, because there is no height map.
  - At 0.10 mm deep the cut still goes through 70 µm copper and isolates
    every net.
  - At 0.30 mm deep it trims 0.027 mm off copper edges, which is harmless.
- **Holes:** 99, all non-plated:

  | Size | 0.75 | 0.80 | 1.00 | 1.10 | 1.20 | 1.30 | 3.20 (M3) |
  |---|---|---|---|---|---|---|---|
  | Count | 4 | 32 | 51 | 2 | 2 | 4 | 4 |

## Files

**For milling (route A):** [`fusion/`](fusion/README.md)

| File | What it is |
|---|---|
| `fusion/cloudline_pcb_MILL_copper_up.step` | **The model to machine**, copper side up as it lies on the machine. It holds the FR-4 body with all holes, and one 0.035 mm copper body per net. The origin is the board's lower-left corner. Z = 0 is the underside; the copper top is at Z = 1.635. |
| `fusion/cloudline_pcb_MILL_copper_up.dxf` | Same view in 2D, in mm. Layers: `ISO_PASS1`/`ISO_PASS2` (isolation tool-centre paths), `DRILL_*` (one per hole size), `OUTLINE`, `COPPER`, `FIDUCIAL` |
| `fusion/cloudline_pcb_tools.json` | Fusion tool library T1–T7, with feeds and speeds for the DI 1000 |
| `fusion/cloudline_pcb_TOPVIEW.step` | The board seen from the parts side, for checks or an enclosure model. **Not for machining.** |
| `fusion/milling_report.txt`, `fusion/isolation_preview.png`, `fusion/mill_preview.png` | Gaps, hole table and cut-width table, and pictures of the paths and copper |

**For editing (Fusion Electronics):** [`eagle/`](eagle/README.md)

| File | What it is |
|---|---|
| `eagle/cloudline_controller.sch` + `.brd` | Schematic and board in EAGLE 9 format, linked, with the parts library embedded |
| `eagle/schematic_preview.png` | What the schematic sheet looks like |

**For ordering or etching (routes B, C):** `fab/`

| File | What it is |
|---|---|
| `fab/cloudline_controller_RevB_gerbers_drill.zip` | **Upload this to the board house.** Gerbers, Excellon drill, and `FAB_NOTES.txt` |
| `fab/gerbers/` | The same files unzipped, plus a drill map (PDF) |
| `fab/bottom_copper_toner_transfer_1to1.pdf` | Bottom copper at 1:1 for toner transfer. Print it as is: laying the print face-down mirrors it correctly. |
| `fab/gerbv_*.png`, `fab/render_*.png` | Renders. The `gerbv_*` ones are drawn from the Gerber files themselves. |
| `fab/drc_report.txt` | KiCad design-rule check report |

**For every route:**

| File | What it is |
|---|---|
| [`fab/assembly_top.pdf`](fab/assembly_top.pdf) | **Assembly drawing at 1:1**: every part outline, reference and pad. On a milled or etched board this replaces the silkscreen. |
| [`fab/pcb_bom.csv`](fab/pcb_bom.csv) | Parts by reference, value and footprint. Part numbers and prices are in [`../bom.csv`](../bom.csv). |
| `cloudline_controller.kicad_pcb`, `.kicad_pro`, `fp-lib-table`, `cloudline.pretty/` | The KiCad 7 project (the master copy) |
| `make_pcb.py`, `make_fab.py`, `drc.py`, `check_pcb.py` | Generate and check the board and the `fab/` files |
| `verify_gerbers.py` | Checks the files in `fab/gerbers/` themselves against the netlist; runs anywhere Python 3.8+ does, no KiCad needed |
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
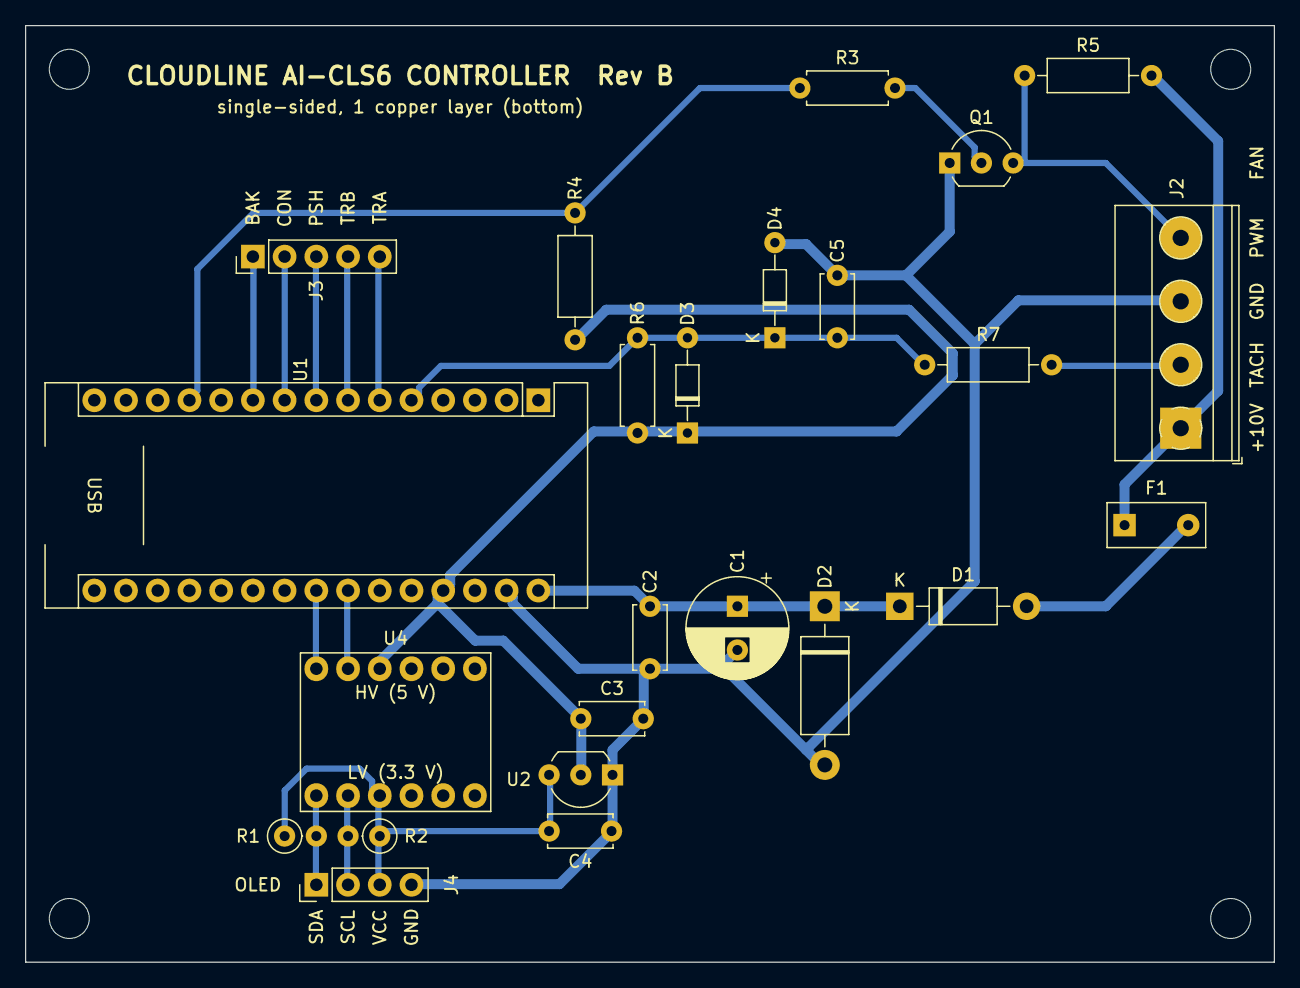
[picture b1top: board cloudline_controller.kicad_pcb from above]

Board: 2 copper layers, 100.0 x 75.0 mm, 28 parts (0 on the bottom side), 20 nets.

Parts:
C1: 220uF 25V; CP_Radial_D8.0mm_P3.50mm
C2: 100nF; C_Disc_D5.0mm_W2.5mm_P5.00mm
C3, C4: 1uF; C_Disc_D5.0mm_W2.5mm_P5.00mm
C5: 10nF; C_Disc_D5.0mm_W2.5mm_P5.00mm
D1: 1N5817; D_DO-41_SOD81_P10.16mm_Horizontal
D2: P6KE13A; D_DO-15_P12.70mm_Horizontal
D3, D4: BAT85; D_DO-34_SOD68_P7.62mm_Horizontal
F1: PTC 0.2A MF-R020; PTC_Radial_P5.10mm
H1, H2, H3, H4: M3; MountingHole_3.2mm_M3
J2: Fan: 1 +10V 2 TACH 3 GND 4 PWM; TerminalBlock_Phoenix_MKDS-1,5-4-5.08_1x04_P5.08mm_Horizont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
J3: OLED keys: BAK CON PSH TRB TRA; PinHeader_1x05_P2.54mm_Vertical
J4: OLED: SDA SCL VCC GND; PinHeader_1x04_P2.54mm_Vertical
Q1: 2N7000; TO-92_Inline_Wide
R1, R2: 2.2k; R_Axial_DIN0207_L6.3mm_D2.5mm_P2.54mm_Vertical
R3: 220; R_Axial_DIN0207_L6.3mm_D2.5mm_P7.62mm_Horizontal
R4: 10k; R_Axial_DIN0207_L6.3mm_D2.5mm_P10.16mm_Horizontal
R5: 4.7k DNP; R_Axial_DIN0207_L6.3mm_D2.5mm_P10.16mm_Horizontal
R6: 10k; R_Axial_DIN0207_L6.3mm_D2.5mm_P7.62mm_Horizontal
R7: 1k; R_Axial_DIN0207_L6.3mm_D2.5mm_P10.16mm_Horizontal
U1: Arduino Nano (socketed); Arduino_Nano
U2: MCP1700-3302E; TO-92_Inline_Wide
U4: SparkFun BOB-12009; SparkFun_BOB-12009

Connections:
+3V3: C4.1, J4.3, R1.1, R2.1, U2.3, U4.LV
+5V: C3.1, D3.1, R4.2, R6.2, U1.27, U2.2, U4.HV
+10V_FAN: F1.1, J2.1, R5.2
+10V_P: C1.1, C2.1, D1.1, D2.1, U1.30
ENC_A: J3.5, U1.6
ENC_B: J3.4, U1.7
ENC_SW: J3.3, U1.8
FAN_PWM: J2.4, Q1.3, R5.1
GATE: Q1.2, R3.2
GND: C1.2, C2.2, C3.2, C4.2, C5.2, D2.2, D4.2, J2.3, J4.4, Q1.1, U1.29, U2.1
KEY_BAK: J3.1, U1.10
KEY_CON: J3.2, U1.9
N_F1_D1: D1.2, F1.2
PWM_D9: R3.1, R4.1, U1.12
SCL_3V3: J4.2, R2.2, U4.LV2
SCL_5V: U1.24, U4.HV2
SDA_3V3: J4.1, R1.2, U4.LV1
SDA_5V: U1.23, U4.HV1
TACH_5V: C5.1, D3.2, D4.1, R6.1, R7.1, U1.5
TACH_IN: J2.2, R7.2

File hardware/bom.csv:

Ref,Qty,Part,Value / rating,Example part number or listing,Package,Approx. unit cost (USD),Notes
U1,1,Arduino Nano (ATmega328P 5 V 16 MHz),Clone with CH340 USB chip is fine,Arduino A000005 (genuine) or ELEGOO Nano V3.0 3-pack (Amazon),Module,8.00,Clone ~$5-8; genuine ~$25. Get one with headers NOT soldered if you will socket it.
U3,1,1.3in OLED + EC11 encoder module,SH1106 128x64 I2C 0x3C; 3.3 V; EC11 20 pulses/20 detents,AITRIP 1.3 inch OLED with EC11 (Amazon ASIN B0F87DZ51P),Module,10.00,Pin labels VCC GND SDA SCL TRA TRB PSH CON BAK; order varies by batch
U2,1,LDO regulator 3.3 V,MCP1700 3.3 V 250 mA; Vin max 6 V,Microchip MCP1700-3302E/TO,TO-92,0.45,Pinout flat face towards you: GND VIN VOUT (check datasheet). PCB: bend the outer leads out to 2.54 mm pitch
Q1,1,N-channel MOSFET,60 V; 200 mA; Vgs(th) 0.8-3 V; Rds(on) <= 5.3 ohm at 4.5 V,onsemi 2N7000TA (or 2N7000BU),TO-92,0.30,Pinout flat face towards you: S G D. PCB: 2.54 mm pitch; bend straight 1.27 mm leads out
D1,1,Schottky diode (reverse-polarity),1 A 20 V,onsemi 1N5817RLG (or Vishay 1N5817-E3/54),DO-41,0.20,Band = cathode = towards +10V_P
D2,1,TVS diode unidirectional,Vrwm 11.1 V; Vbr 12.4-13.7 V; 600 W,Littelfuse P6KE13A,DO-15,0.45,Use P6KE15A if the fan rail measures above 10.8 V
D3 D4,2,Small-signal Schottky diode (tach clamps),30 V 200 mA,Nexperia BAT85 (BAT85.133) or Vishay BAT85-TAP,DO-34,0.15,Band = cathode. D3 cathode to +5V; D4 cathode to tach node
F1,1,PTC resettable fuse,0.20 A hold; 0.40 A trip; 60 V,Bourns MF-R020,Radial 5.1 mm,0.35,PCB footprint: straight leads 5.1 mm apart
C1,1,Aluminium electrolytic capacitor,220 uF 25 V (or 35 V) 105 C,Panasonic EEU-FR1E221 (or Nichicon UVR1E221MED),Radial 8 mm,0.40,Observe polarity: stripe = negative
C2,1,Ceramic capacitor,100 nF 50 V X7R,TDK FG28X7R1H104KNT06,Radial 5.0 mm,0.25,5 mm lead pitch fits the PCB footprint
C3 C4,2,Ceramic capacitor,1 uF 25 V X7R,TDK FG28X7R1E105KRT06,Radial 5.0 mm,0.30,MCP1700 needs >= 1 uF on input and output; 5 mm lead pitch for the PCB
C5,1,Ceramic capacitor,10 nF 50 V X7R,TDK FG28X7R1H103KNT06,Radial 5.0 mm,0.25,PCB needs 5 mm lead pitch (FG28 family; check the datasheet of the exact part)
U4,1,Bidirectional I2C level shifter (BSS138),2 channels used; 5 V HV side / 3.3 V LV side; 10 kohm pull-ups on board,SparkFun BOB-12009,Module,3.95,Between Nano A4/A5 (HV) and OLED SDA/SCL (LV). Solder header pins.
R1 R2,2,Resistor,2.2 kohm 1/4 W 5 %,Yageo CFR-25JB-52-2K2,Axial,0.10,I2C pull-ups to +3V3 (2.2k for 400 kHz rise time)
R3,1,Resistor,220 ohm 1/4 W 5 %,Yageo CFR-25JB-52-220R,Axial,0.10,Q1 gate series
R4,1,Resistor,10 kohm 1/4 W 5 %,Yageo CFR-25JB-52-10K,Axial,0.10,Q1 gate pull-up: keeps fan OFF during reset/boot
R5,1,Resistor (do not populate by default),4.7 kohm 1/4 W 5 %,Yageo CFR-25JB-52-4K7,Axial,0.10,Fit only if the PWM line floats (pre-connection check M3)
R6,1,Resistor,10 kohm 1/4 W 5 %,Yageo CFR-25JB-52-10K,Axial,0.10,Tach pull-up to +5V
R7,1,Resistor,1 kohm 1/4 W 5 %,Yageo CFR-25JB-52-1K0,Axial,0.10,Tach series / clamp current limit
J1,1,4-pin PC peripheral (Molex 8981) extension cable,Male-to-female; 18-20 AWG; 30 cm,StarTech.com LP4POWEXT12 (or any 4-pin Molex extension),Cable,4.00,Cut in half; keep the end that plugs into the fan's control lead (PCB: its wires go into J2)
-,1,Perfboard (protoboard) - perfboard build only,5 x 7 cm double-sided 2.54 mm pitch,ElectroCookie or generic 5x7 cm FR4 protoboard,Board,1.00,Not needed with the PCB
-,2,Female header strip for Nano socket,1 x 15 pin 2.54 mm,Sullins PPTC151LFBN-RC,Through-hole,1.00,Lets you unplug the Nano; optional
-,1,Female-female jumper wires (OLED module),20 cm 2.54 mm Dupont; 10 needed,Generic 40-pin F-F Dupont ribbon (Amazon),Wire,3.00,Or solder 24-26 AWG wire directly
-,1,Hook-up wire,22 AWG stranded (power) and 24-26 AWG stranded (signals); several colours,Generic silicone wire kit (e.g. Striveday 22 AWG 6 colours),Wire,8.00,Colours per hardware/wiring.svg
-,1,Heat-shrink tubing assortment,2-6 mm 2:1 polyolefin,Generic 2:1 assortment kit,Tubing,6.00,For the J1 cable splices and exposed leads
-,1,Enclosure,"ABS box; INSIDE at least 115 x 90 x 35 mm for the PCB (100 x 75 mm board clear of corner screw posts), or 75 x 60 x 35 mm for the perfboard","e.g. a Hammond 1591-series box chosen from its drawing (inside size and boss positions), or 3D-printed",Box,8.00,Mount the board on 4 x M3 standoffs through its own holes; cut a window for the OLED and a 7 mm hole for the encoder shaft
-,1,Cable gland,PG7 for 3-6.5 mm cable,Generic nylon PG7 gland,Hardware,0.50,Strain relief for the fan cable
-,4,Standoffs and screws,M2.5 or M3 x 6-10 mm nylon,Generic nylon standoff kit,Hardware,0.25,Mount the perfboard and OLED module
-,1,Knob for EC11 D-shaft,6 mm,Generic 6 mm D-shaft knob,Hardware,1.00,Optional; some modules include one
PCB,1,Printed circuit board - PCB build only,"100 x 75 mm, 1 copper layer, FR-4 1.6 mm",hardware/pcb/fab/cloudline_controller_RevB_gerbers_drill.zip (order from any board house),Board,2.00,Replaces the perfboard; see hardware/pcb/README.md
J2,1,4-way screw terminal - PCB build only,5.08 mm pitch; 1.5 mm2 wire,Phoenix Contact MKDS 1/4-5.08 (1715747),Through-hole,1.50,Fan cable connection: 1 +10V 2 TACH 3 GND 4 PWM (labelled on the board)
J3,1,Pin header - PCB build only,1 x 5 male 2.54 mm,Generic 2.54 mm break-away male header,Through-hole,0.10,OLED keys/encoder (BAK CON PSH TRB TRA)
J4,1,Pin header - PCB build only,1 x 4 male 2.54 mm,Generic 2.54 mm break-away male header,Through-hole,0.10,OLED power/I2C (SDA SCL VCC GND)

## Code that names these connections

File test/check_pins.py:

#!/usr/bin/env python3
"""Cross-check every pin assignment across the firmware, the schematic, the
wiring view, PINOUT.md and README.md. Exits non-zero on any mismatch.

    python3 test/check_pins.py        (from the repository root)
"""

import os
import re
import sys

ROOT = os.path.dirname(os.path.dirname(os.path.abspath(__file__)))


def read(rel):
    with open(os.path.join(ROOT, rel), encoding="utf-8") as f:
        return f.read()


# Arduino Nano physical pin numbers (header pin 1 = D1/TX).
NANO_PHYS = {"D1": 1, "D0": 2, "GND_A": 4, "D2": 5, "D3": 6, "D4": 7, "D5": 8, "D6": 9,
             "D7": 10, "D8": 11, "D9": 12, "D10": 13, "D11": 14, "D12": 15, "D13": 16,
             "3V3": 17, "A4": 23, "A5": 24, "5V": 27, "GND_B": 29, "VIN": 30}

# signal: (config.h macro or None, Nano pin, module label or None, wiring.py net)
SIGNALS = [
    ("TACH", "PIN_TACH", "D2", None, "TACH_D2"),
    ("ENC_A", "PIN_ENC_A", "D3", "TRA", "TRA"),
    ("ENC_B", "PIN_ENC_B", "D4", "TRB", "TRB"),
    ("ENC_SW", "PIN_ENC_SW", "D5", "PSH", "PSH"),
    ("KEY_CON", "PIN_KEY_CON", "D6", "CON", "CON"),
    ("KEY_BAK", "PIN_KEY_BAK", "D7", "BAK", "BAK"),
    ("FAN_PWM", "PIN_FAN_PWM", "D9", None, "GATE"),
    ("STATUS_LED", "PIN_STATUS_LED", "D13", None, None),
    ("SDA", None, "A4", "SDA", "SDA"),
    ("SCL", None, "A5", "SCL", "SCL"),
    ("VIN", None, "VIN", None, "VIN"),
    ("+5V", None, "5V", None, "+5V"),
]

rows = []
failures = 0


def check(name, source, ok, detail=""):
    global failures
    rows.append((name, source, "ok" if ok else "MISMATCH", detail))
    if not ok:
        failures += 1


cfg = read("firmware/cloudline_controller/config.h")
sch = read("hardware/schematic.py")
wir = read("hardware/wiring.py")
pin = read("PINOUT.md")
rd = read("README.md")

# Schematic: Nano pins drawn with pin_l/pin_r(x, y, "LABEL", physical), the
# variable name they are assigned to, and the module pins they are wired to.
sch_nano = {}
for var, label, num in re.findall(r'(n_\w+) = pin_[lr]\([^,]+, \d+, "([^"]+)", (\d+)\)', sch):
    sch_nano[var] = (label, int(num))
sch_mod = dict(re.findall(r'(m_\w+) = pin_l\([^,]+, \d+, "([^"]+)"', sch))
sch_wires = re.findall(r'wire\((n_\w+), (m_\w+)\)', sch)

# Wiring view: wire(net, [(px[("T"|"B", "PIN")] ...  and OLED pins by net name.
wir_pins = {}
# (a) loops over ("NET", "PIN") pairs; (b) wire("NET", [... px[("T", "PIN")] ...])
for net, p in re.findall(r'\("([A-Z+_0-9]+)", "([AD]\d+|5V|GND|VIN)"\)', wir):
    wir_pins.setdefault(net, set()).add(p)
for net, p in re.findall(r'wire\("([^"]+)", \[[^;]*?px\[\("[TB]", "([^"]+)"\)\]', wir, re.S):
    wir_pins.setdefault(net, set()).add(p)

for sig, macro, npin, mod, wnet in SIGNALS:
    num = int(npin[1:]) if npin.startswith("D") else None
    phys = NANO_PHYS.get(npin)
    # 1. firmware
    if macro:
        m = re.search(r"#define\s+%s\s+(\d+)" % macro, cfg)
        check(sig, "config.h", bool(m) and int(m.group(1)) == num,
              f"{macro} = {m.group(1) if m else 'missing'} (expected {num})")
    # 2. schematic: a Nano pin whose label starts with the pin name and whose
    #    physical number matches; and, for module signals, a wire to that label.
    hits = [(v, l, n) for v, (l, n) in sch_nano.items()
            if l.split(" / ")[0].replace("+", "") in (npin, npin.replace("D", "D"))
            or l.startswith(npin + " ")]
    if npin == "5V":
        hits = [(v, l, n) for v, (l, n) in sch_nano.items() if l == "+5V"]
    if sig != "STATUS_LED":
        ok = any(n == phys for _, _, n in hits)
        check(sig, "schematic", ok, f"{[(l, n) for _, l, n in hits]} (expected {npin} = pin {phys})")
        if mod and sig in ("SDA", "SCL"):
            # through the level shifter U4: Nano pin -> U4 HVn, U4 LVn -> module pin
            y = {"SDA": 460, "SCL": 500}[sig]
            nv = [v for v, _, _ in hits][0] if hits else "?"
            ok = (f"wire({nv}, (ux4, {y}))" in sch and
                  f"wire((ux4 + uw4, {y}), m_{sig.lower()})" in sch and
                  sch_mod.get(f"m_{sig.lower()}", "").startswith(mod))
            check(sig, "schematic wire", ok, f"{npin} -> U4 -> {mod}")
        elif mod:
            nvars = {v for v, _, _ in hits}
            wired = [sch_mod.get(m, "?") for nv, m in sch_wires if nv in nvars]
            check(sig, "schematic wire", any(w.startswith(mod) for w in wired),
                  f"{npin} wired to {wired} (expected {mod})")
    # 3. wiring view
    if wnet:
        label = {"5V": "5V"}.get(npin, npin)
        check(sig, "wiring.svg", label in wir_pins.get(wnet, set()),
              f"net {wnet} -> {sorted(wir_pins.get(wnet, set()))} (expected {label})")
    # 4. PINOUT.md section 3 table row: "| phys | **NAME** ..."
    if phys:
        pname = {"5V": r"\+5V", "VIN": "VIN"}.get(npin, npin)
        row = re.search(r"^\| %d \| \*\*%s\*\*[^\n]*" % (phys, pname), pin, re.M)
        if sig == "STATUS_LED":
            row = re.search(r"^\| %d \| %s [^\n]*" % (phys, npin), pin, re.M)
        ok = bool(row)
        if ok and macro:
            ok = f"`{macro} {num}`" in row.group(0)
        if ok and mod:
            ok = f"**{mod}**" in row.group(0)
        check(sig, "PINOUT.md", ok, row.group(0)[:70] if row else f"no row for pin {phys} {npin}")
    # 5. README build step 4 table (module wiring) and step 6 text
    if mod:
        if sig in ("SDA", "SCL"):  # via the level shifter U4
            r = re.search(r"^ *\| %s \| U4 LV\d [^|]*socket %s \(pin %d\)" % (mod, npin, phys), rd, re.M)
        else:
            r = re.search(r"^ *\| %s \| socket %s \(pin %d\)" % (mod, npin, phys), rd, re.M)
        check(sig, "README.md", bool(r), r.group(0) if r else f"no '| {mod} | socket {npin} (pin {phys})' row")
    elif sig in ("FAN_PWM", "TACH"):
        r = re.search(r"socket \*\*%s\*\* \(pin %d\)" % (npin, phys), rd)
        check(sig, "README.md", bool(r), r.group(0) if r else f"no 'socket **{npin}** (pin {phys})'")
    elif sig in ("VIN", "+5V"):
        word = {"VIN": r"\*\*VIN\*\* pin \(30\)", "+5V": r"\*\*\+5V\*\* pin \(27\)"}[sig]
        r = re.search(word, rd)
        check(sig, "README.md", bool(r), r.group(0) if r else f"no {word}")

# J1 pin functions: schematic, wiring view, PINOUT.md
j1 = {4: "+10V", 3: "GND", 2: "PWM", 1: "TACH"}
for n, f in j1.items():
    check(f"J1.{n}", "schematic", re.search(r'pin_r\([^)]*"%s", %d,' % (re.escape(f), n), sch) is not None, f)
    check(f"J1.{n}", "wiring.svg", re.search(r'%d: \("%s", \d+\)' % (n, re.escape(f)), wir) is not None, f)
    check(f"J1.{n}", "PINOUT.md", re.search(r"^\| \*\*%d\*\* \|" % n, pin, re.M) is not None, f)

w = max(len(r[0]) for r in rows)
for name, src, status, detail in rows:
    print(f"{name:<{w}}  {src:<15} {status:<8} {detail}")
print(f"\npin cross-check: {len(rows)} checks, {failures} mismatches")
sys.exit(1 if failures else 0)
